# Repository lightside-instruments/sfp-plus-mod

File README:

sfp-plus-mod is an open hardware SFP+
breakout module board published by Lightside Instruments AS.

Up to release sfp-plus-mod-1.3 the project provided schematics and
PCB design files for KiCAD. Since sfp-plus-mod-1.3-1
OpenSCAD design of a 3d printable mechanical enclosure conforming
with minor exceptions to SFF-8432 Rev 5.2a
was added - mechanical.scad.

The project is published by Lightside Instruments AS
under TAPR Open Hardware License. Read the LICENSE file
for details.

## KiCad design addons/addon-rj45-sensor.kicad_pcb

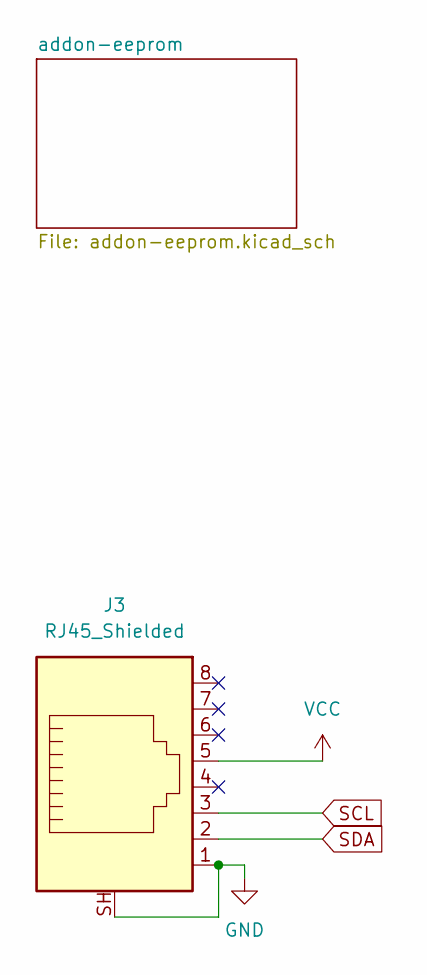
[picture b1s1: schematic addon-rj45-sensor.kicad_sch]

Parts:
J3: RJ45_Shielded; RJ45_Amphenol_RJHSE5380

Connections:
GND: J3.1, J3.SH; also elsewhere on the board
SCL: J3.3; also elsewhere on the board
SDA: J3.2; also elsewhere on the board
VCC: J3.5; also elsewhere on the board

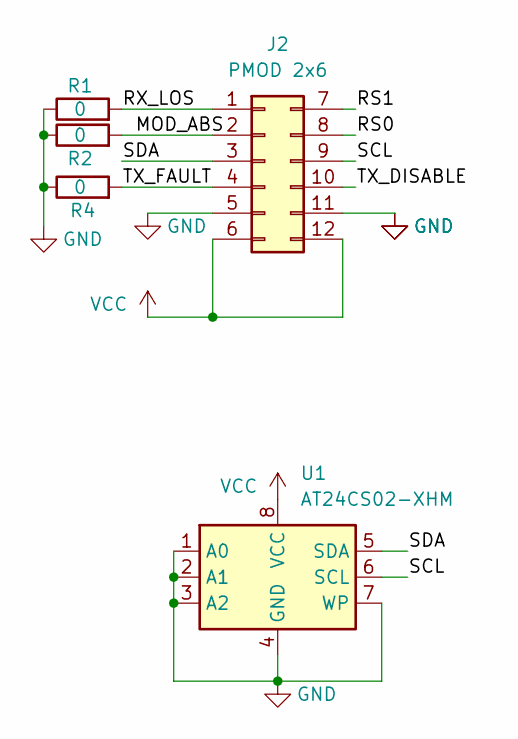
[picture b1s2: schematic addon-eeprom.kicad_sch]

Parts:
J2: PMOD 2x6; PinSocket_2x06_P2.54mm_Vertical_1to6_7to12
R1, R2, R4: 0; R_0402_1005Metric
U1: AT24CS02-XHM; TSSOP-8_4.4x3mm_P0.65mm

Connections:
/addon-eeprom/MOD_ABS: J2.2, R2.2
/addon-eeprom/RS0: J2.8
/addon-eeprom/RS1: J2.7
/addon-eeprom/RX_LOS: J2.1, R1.2
/addon-eeprom/TX_DISABLE: J2.10
/addon-eeprom/TX_FAULT: J2.4, R4.2
GND: J2.5, J2.11, R1.1, R2.1, R4.1, U1.1 (A0), U1.2 (A1), U1.3 (A2), U1.4 (GND), U1.7 (WP); also elsewhere on the board
SCL: J2.9, U1.6 (SCL); also elsewhere on the board
SDA: J2.3, U1.5 (SDA); also elsewhere on the board
VCC: J2.6, J2.12, U1.8 (VCC); also elsewhere on the board

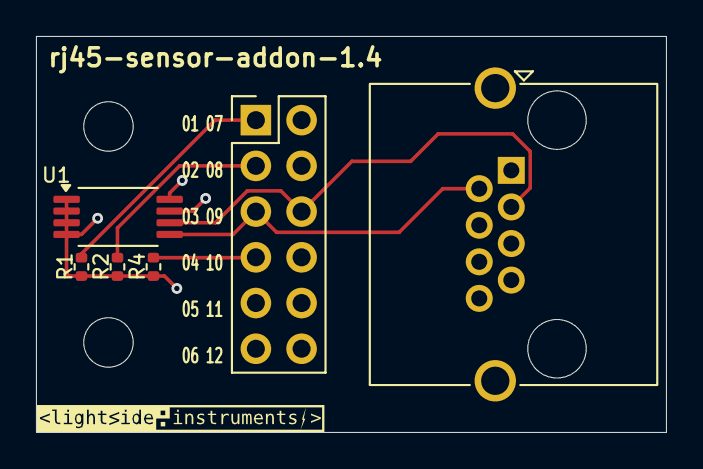
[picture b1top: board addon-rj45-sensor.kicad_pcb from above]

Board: 4 copper layers, 35.0 x 22.0 mm, 7 parts (0 on the bottom side), 7 nets.

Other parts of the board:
svg2mod: G***; lsi-logo-16mm

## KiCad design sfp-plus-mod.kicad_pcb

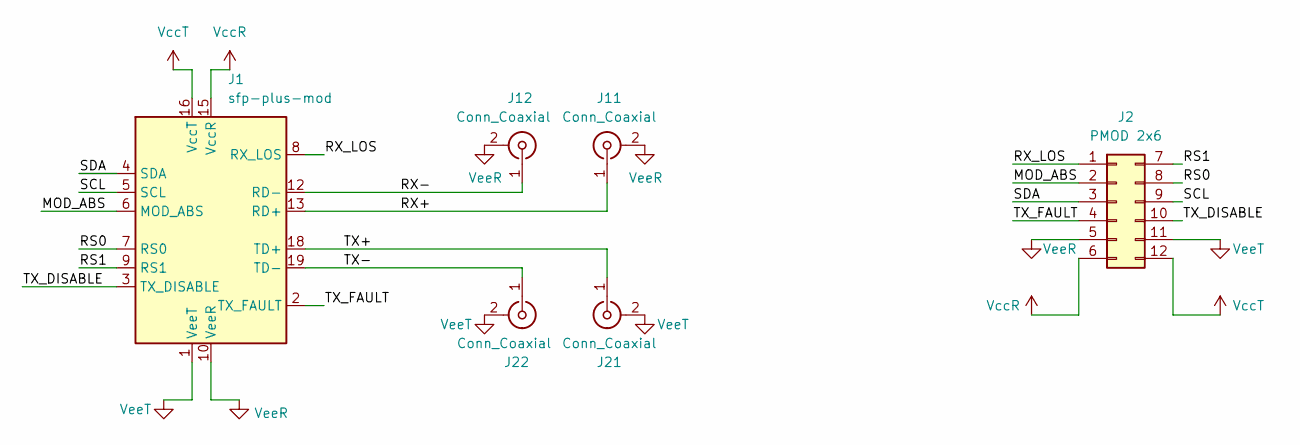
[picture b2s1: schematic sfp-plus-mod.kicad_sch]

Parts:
J1: sfp-plus-mod
J2: PMOD 2x6; PinSocket_2x06_P2.54mm_Vertical_1to6_7to12
J11, J12, J21: Conn_Coaxial; SMA_Wurth_60312002114503_Vertical
J22: Conn_Coaxial; SMA_Amphenol_901-144_Vertical

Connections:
/MOD_ABS: J1.6 (MOD_ABS), J2.2
/RS0: J1.7 (RS0), J2.8
/RS1: J1.9 (RS1), J2.7
/RX+: J1.13 (RD+), J11.1 (In)
/RX-: J1.12 (RD-), J12.1 (In)
/RX_LOS: J1.8 (RX_LOS), J2.1
/SCL: J1.5 (SCL), J2.9
/SDA: J1.4 (SDA), J2.3
/TX+: J1.18 (TD+), J21.1 (In)
/TX-: J1.19 (TD-), J22.1 (In)
/TX_DISABLE: J1.3 (TX_DISABLE), J2.10
/TX_FAULT: J1.2 (TX_FAULT), J2.4
VccR: J1.15 (VccR), J2.6
VccT: J1.16 (VccT), J2.12
VeeR: J1.10 (VeeR), J1.11 (VeeR), J1.14 (VeeR), J2.5, J11.2 (Ext), J12.2 (Ext)
VeeT: J1.1 (VeeT), J1.17 (VeeT), J1.20 (VeeT), J2.11, J21.2 (Ext), J22.2 (Ext)

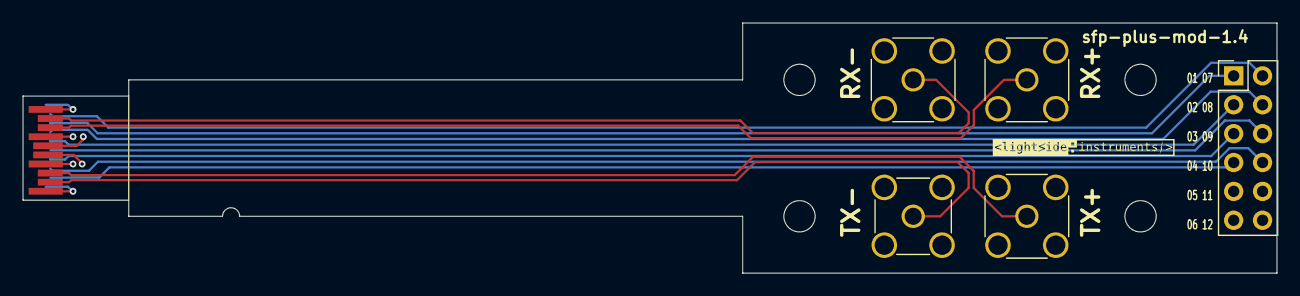
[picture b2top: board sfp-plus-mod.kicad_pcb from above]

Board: 4 copper layers, 110.3 x 22.0 mm, 7 parts (0 on the bottom side), 16 nets.

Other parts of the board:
svg2mod: G***; lsi-logo-16mm

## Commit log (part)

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2025-01-29 sfp-plus-mod-1.0
2025-01-29 sfp-plus-mod-1.1
2025-02-25 sfp-plus-mod-1.2
2025-07-04 sfp-plus-mod-1.3
2025-07-18 sfp-plus-mod-1.3-1
2025-07-24 sfp-plus-mod-1.3-2
2025-07-24 sfp-plus-mod-1.3-3
